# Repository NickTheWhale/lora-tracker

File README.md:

# lora-tracker
digikey cart: http://www.digikey.com/short/pwb05w9p

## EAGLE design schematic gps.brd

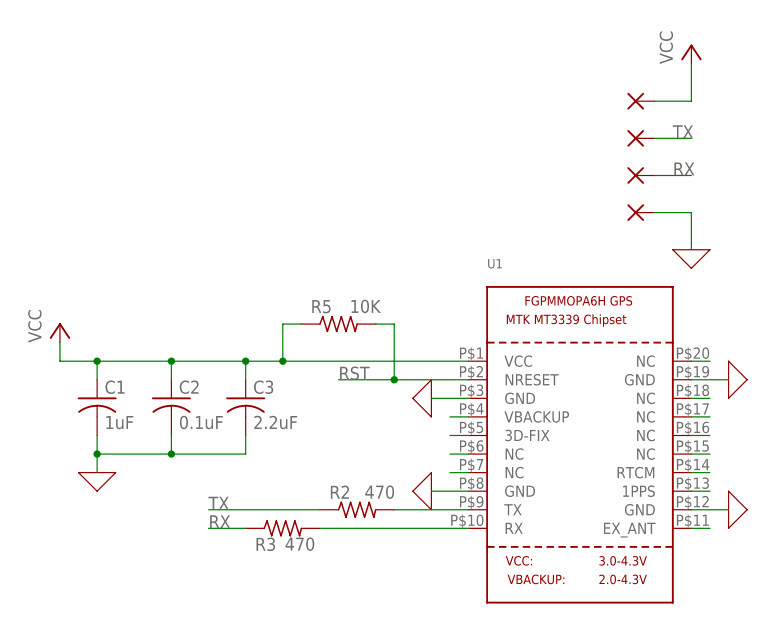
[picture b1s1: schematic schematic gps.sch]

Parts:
C1: 1uF; C0805
C2: 0.1uF; C0805
C3: 2.2uF; C0805
GND: WIREPADSMD1,27-254; SMD1,27-2,54
R2, R3: 470; R0805
R5: 10K; R0805
RX: WIREPADSMD1,27-254; SMD1,27-2,54
TX: WIREPADSMD1,27-254; SMD1,27-2,54
U1: GPS_FGPMMOPA6H; FGPMMOPA6H
VCC: WIREPADSMD1,27-254; SMD1,27-2,54

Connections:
0: C1.2, C2.2, C3.2, GND.1, U1.P$3 (GND), U1.P$8 (GND), U1.P$12 (GND), U1.P$19 (GND)
unnamed: R2.2, U1.P$9 (TX)
unnamed: R3.2, U1.P$10 (RX)
RST: R5.2, U1.P$2 (NRESET)
RX: R3.1, RX.1
TX: R2.1, TX.1
VCC: C1.1, C2.1, C3.1, R5.1, U1.P$1 (VCC), VCC.1

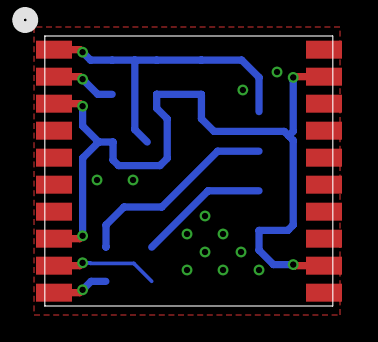
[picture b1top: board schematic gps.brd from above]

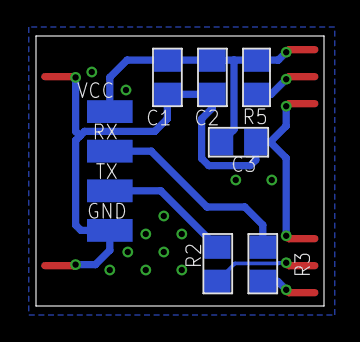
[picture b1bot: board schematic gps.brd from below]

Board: 2 copper layers, 16.0 x 15.0 mm, 11 parts (10 on the bottom side), 7 nets.

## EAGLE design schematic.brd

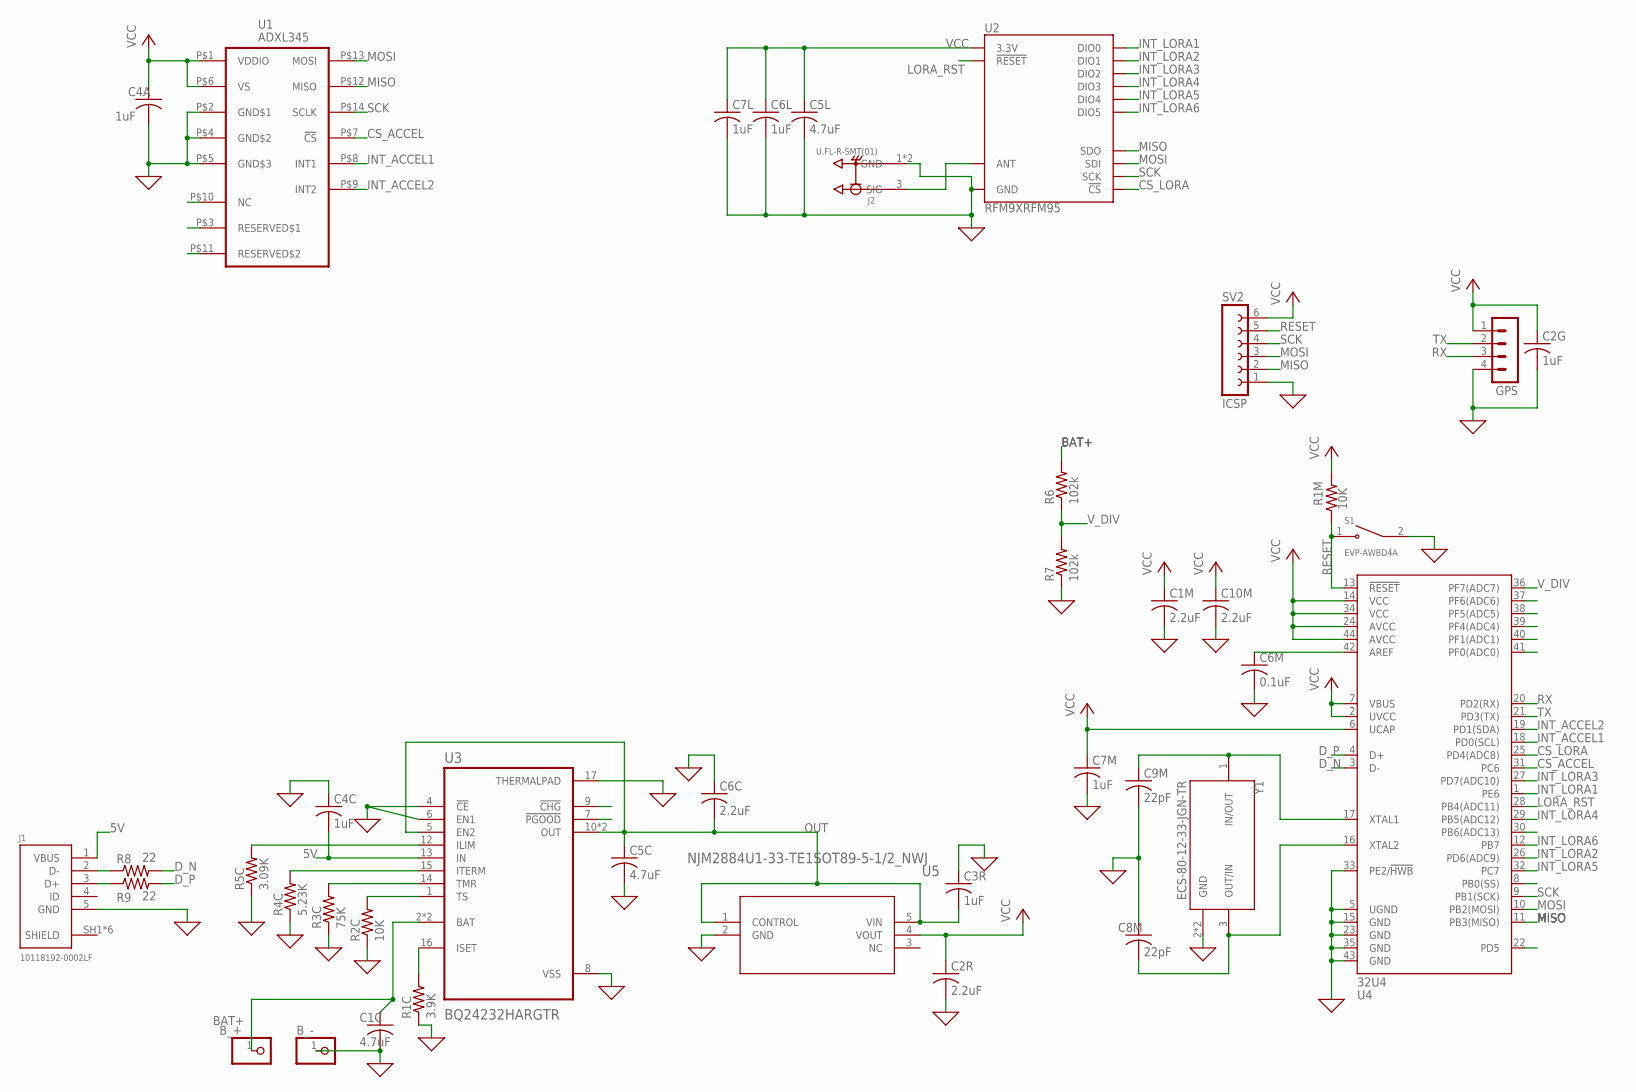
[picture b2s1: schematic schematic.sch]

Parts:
B_+: PINHD-1X1; 1X01
B_-: PINHD-1X1; 1X01
C1C, C5C, C5L: 4.7uF; C0805
C1M, C2R, C6C, C10M: 2.2uF; C0805
C2G, C3R, C4A, C4C, C6L, C7L, C7M: 1uF; C0805
C6M: 0.1uF; C0805
C8M, C9M: 22pF; C0805
GPS: MA04-1
J1: 10118192-0002LF
J2: U.FL-R-SMT(01); HRS_U.FL-R-SMT(01)
R1C: 3.9K; R0805
R1M, R2C: 10K; R0805
R3C: 75K; R0805
R4C: 5.23K; R0805
R5C: 3.09K; R0805
R6, R7: 102k; R0805
R8, R9: 22; R0805
S1: EVP-AWBD4A; SW_EVP-AWBD4A
SV2: ICSP; FE06
U1: ADXL345; LGA14
U2: RFM9XRFM95; RFM95
U3: BQ24232HARGTR; QFN50P300X300X100-17N
U4: 32U4; QFN-44
U5: NJM2884U1-33-TE1SOT89-5-1/2_NWJ; SOT89-5-1/2_NWJ
Y1: ECS-80-12-33-JGN-TR; XTAL_ECS-240-8-33-AGN-TR

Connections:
0: B_-.1, C1C.2, C1M.2, C2G.2, C2R.2, C3R.1, C4A.2, C4C.1, C5C.2, C5L.2, C6C.1, C6L.2, C6M.2, C7L.2, C7M.2, C8M.1, C9M.2, C10M.2, GPS.4, J1.5 (GND), J2.1 (GND), J2.2 (GND), R1C.1, R2C.1, R3C.1, R4C.1, R5C.1, R7.1, S1.2 (COM), SV2.1, U1.P$2 (GND$1), U1.P$4 (GND$2), U1.P$5 (GND$3), U2.GND@1 (GND), U2.GND@2 (GND), U2.GND@3 (GND), U3.4 (!CE), U3.6 (EN1), U3.8 (VSS), U3.17 (THERMALPAD), U4.5 (UGND), U4.15 (GND), U4.23 (GND), U4.33 (PE2/!HWB), U4.35 (GND), U4.43 (GND), U5.2 (GND), Y1.2 (GND), Y1.4 (GND)
5V: C4C.2, J1.1 (VBUS), U3.13 (IN)
BAT+: B_+.1, C1C.1, R6.2, U3.2 (BAT), U3.3 (BAT)
CS_ACCEL: U1.P$7 (!CS), U4.31 (PC6)
CS_LORA: U2.NSS (!CS!), U4.25 (PD4(ADC8))
D_N: R8.2, U4.3 (D-)
D_P: R9.2, U4.4 (D+)
INT_ACCEL1: U1.P$8 (INT1), U4.18 (PD0(SCL))
INT_ACCEL2: U1.P$9 (INT2), U4.19 (PD1(SDA))
INT_LORA1: U2.DIO0, U4.1 (PE6)
INT_LORA2: U2.DIO1, U4.26 (PD6(ADC9))
INT_LORA3: U2.DIO2, U4.27 (PD7(ADC10))
INT_LORA4: U2.DIO3, U4.29 (PB5(ADC12))
INT_LORA5: U2.DIO4, U4.32 (PC7)
INT_LORA6: U2.DIO5, U4.12 (PB7)
LORA_RST: U2.!RESET, U4.28 (PB4(ADC11))
MISO: SV2.2, U1.P$12 (MISO), U2.SDO, U4.11 (PB3(MISO))
MOSI: SV2.3, U1.P$13 (MOSI), U2.SDI, U4.10 (PB2(MOSI))
unnamed: J1.2 (D-), R8.1
unnamed: J1.3 (D+), R9.1
unnamed: R5C.2, U3.12 (ILIM)
unnamed: R4C.2, U3.15 (ITERM)
unnamed: R3C.2, U3.14 (TMR)
unnamed: J2.3 (SIG), U2.ANT
unnamed: R2C.2, U3.1 (TS)
unnamed: R1C.2, U3.16 (ISET)
unnamed: C8M.2, U4.16 (XTAL2), Y1.3 (OUT/IN)
unnamed: C9M.1, U4.17 (XTAL1), Y1.1 (IN/OUT)
unnamed: C6M.1, U4.42 (AREF)
OUT: C3R.2, C5C.1, C6C.2, U3.5 (EN2), U3.10 (OUT), U3.11 (OUT), U5.1 (CONTROL), U5.5 (VIN)
RESET: R1M.1, S1.1 (NO), SV2.5, U4.13 (!RESET)
RX: GPS.3, U4.20 (PD2(RX))
SCK: SV2.4, U1.P$14 (SCLK), U2.SCK, U4.9 (PB1(SCK))
SHIELD: J1.SH1 (SHIELD), J1.SH2 (SHIELD), J1.SH3 (SHIELD), J1.SH4 (SHIELD), J1.SH5 (SHIELD), J1.SH6 (SHIELD)
TX: GPS.2, U4.21 (PD3(TX))
VCC: C1M.1, C2G.1, C2R.1, C4A.1, C5L.1, C6L.1, C7L.1, C7M.1, C10M.1, GPS.1, R1M.2, SV2.6, U1.P$1 (VDDIO), U1.P$6 (VS), U2.3.3V, U4.2 (UVCC), U4.6 (UCAP), U4.7 (VBUS), U4.14 (VCC), U4.24 (AVCC), U4.34 (VCC), U4.44 (AVCC), U5.4 (VOUT)
V_DIV: R6.1, R7.2, U4.36 (PF7(ADC7))

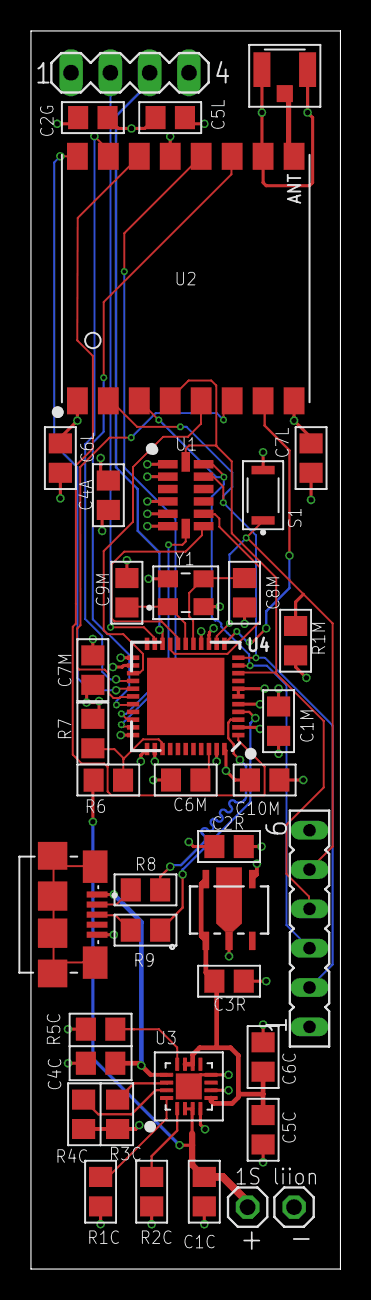
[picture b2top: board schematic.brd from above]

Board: 4 copper layers, 20.0 x 80.0 mm, 40 parts (0 on the bottom side), 37 nets.

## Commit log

2022-03-09 added default wifi credentials
2022-03-09 Rename 32u4_working_tx.ino to lora tx.ino
2022-03-09 Rename esp32_lora_rx_with_wifi_portal.ino to lora rx.ino
2022-03-09 oled support
2022-03-10 more oled stuff
2022-03-10 #define CRC
2022-03-10 oled
2022-03-10 bit map giggity

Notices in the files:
parts and their libraries:
SparkFun-RF: Licensing: Creative Commons ShareAlike 4.0 International - https://creativecommons.org/licenses/by-sa/4.0
COPYRIGHT: Copyright (C) 2021 Ultra Librarian. All rights reserved.
